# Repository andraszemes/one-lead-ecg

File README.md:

# One Lead ECG

The objective of this project was to create a working single lead EKG. The work process was divided into several stages to provide clarity and a productive development framework. Firstly, the hardware had to be layed out, manufactured and constructed. Then followed the phase of software design, development and deployment on different application layers. The finished product encompasses both physical and intellectual components.

The device measures biopotentials using body-surface electrodes. After amplification the signal is processed and filtered by a programmable microchip. Next, the filtered data gets transferred into the computer, where a program plots out the resulting graph. The input stream can be saved for later use either as a visual snapshot or as a data file.

A lot can be learned from such a comprehensive, theoretically and practically challanging undertaking. Let the subject of this project be a testimony to the importance of interdisciplinary research and exchange of knowledge.

## Hardware

The circuit schematic and PCB design is available in the /hardware folder. The design files were created in Eagle.

### Prerequisites

For the desktop application make sure the Java Runtime Environment is installed.

## Web interface demo

The web interface is currently available on [the demo site](http://ekg.epizy.com/).

### Desktop app installation

The distribution binaries are located in /software/heart_rate_monitor/dist. Alternatively you can use the Serial Plotter of the Arduino IDE.

Linux terminal:

```
./heart_rate_monitor
```

Windows CLI:

```
heart_rate_monitor.exe
```

## Built With

* [Arduino IDE](https://www.arduino.cc/en/main/software) - Microchip programming
* [Eagle](https://www.autodesk.com/products/eagle/overview) - PCB design software
* [Processing](https://processing.org/) - Visual desktop application
* [Bootstrap](https://getbootstrap.com/) - The web framework used
* [CanvasJS](https://canvasjs.com/) - Graph plotting API on the web

## Authors

* **András Zemes** - *Project developer* - [andraszemes](https://github.com/andraszemes)

## Acknowledgments

* [Scott W harden](https://www.swharden.com/wp/)
* [Casey Kuhns](https://github.com/sparkfun/AD8232_Heart_Rate_Monitor)
* [Pieter Pas](https://github.com/tttapa/Filters)

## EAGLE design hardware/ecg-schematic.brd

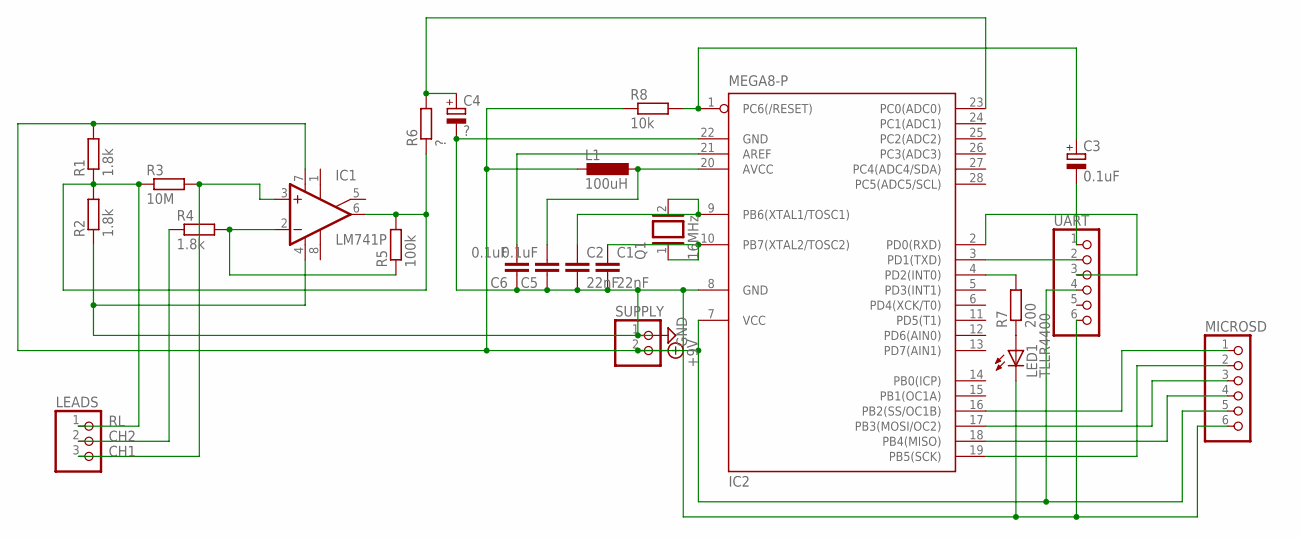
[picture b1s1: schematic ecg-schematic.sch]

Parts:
C1, C2: 22nF; C025-025X050
C3: 0.1uF; B45181A
C4: ?; ETR1
C5, C6: 0.1uF; C025-025X050
IC1: LM741P; DIL08
IC2: MEGA8-P; DIL28-3
L1: 100uH; 0204/5
LEADS: PINHD-1X3; 1X03
LED1: TLLR4400; LED3MM
MICROSD: PINHD-1X6; 1X06
Q1: 16MHz; QS
R1, R2, R4: 1.8k; 0204/7
R3: 10M; 0204/7
R5: 100k; 0204/7
R6: ?; 0204/7
R7: 200; 0204/7
R8: 10k; 0204/7
SUPPLY: PINHD-1X2; 1X02
UART: PINHD-1X6; 1X06

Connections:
+9V: IC1.7 (V+), IC2.7 (VCC), L1.2, MICROSD.5, R1.2, R8.1, SUPPLY.2, UART.4
CH1: IC1.3 (+IN), LEADS.3, R3.2
CH2: LEADS.2, R4.1
GND: C1.2, C2.2, C4.-, C5.1, C6.1, IC1.4 (V-), IC2.8 (GND), IC2.22 (GND), LED1.K (C), MICROSD.6, R2.1, SUPPLY.1, UART.6
unnamed: C2.1, IC2.9 (PB6(XTAL1/TOSC1)), Q1.2
unnamed: C1.1, IC2.10 (PB7(XTAL2/TOSC2)), Q1.1
unnamed: IC1.2 (-IN), R4.2, R5.1
unnamed: C3.-, UART.1
unnamed: C3.+, IC2.1 (PC6(/RESET)), R8.2
unnamed: IC2.3 (PD1(TXD)), UART.2
unnamed: IC2.2 (PD0(RXD)), UART.3
unnamed: C4.+, IC2.23 (PC0(ADC0)), R6.2
unnamed: IC2.16 (PB2(SS/OC1B)), MICROSD.1
unnamed: IC2.19 (PB5(SCK)), MICROSD.2
unnamed: IC2.17 (PB3(MOSI/OC2)), MICROSD.3
unnamed: IC2.18 (PB4(MISO)), MICROSD.4
unnamed: LED1.A, R7.1
unnamed: IC2.4 (PD2(INT0)), R7.2
unnamed: C5.2, IC2.20 (AVCC), L1.1
unnamed: C6.2, IC2.21 (AREF)
RL: IC1.6 (OUT), LEADS.1, R1.1, R2.2, R3.1, R5.2, R6.1

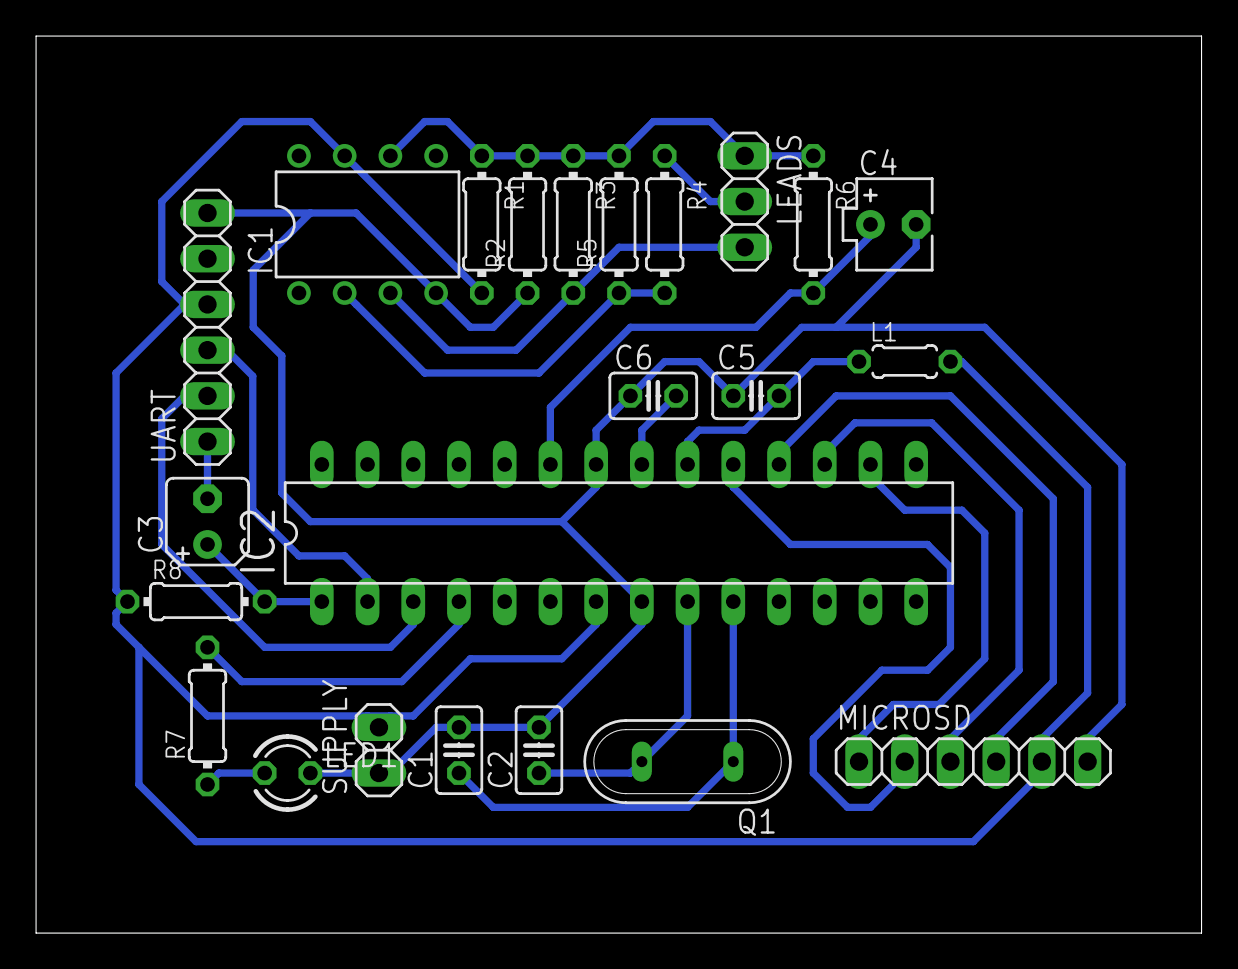
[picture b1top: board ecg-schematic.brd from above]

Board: 2 copper layers, 64.8 x 49.8 mm, 23 parts (0 on the bottom side), 21 nets.

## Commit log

2018-12-19 Initial commit.
2019-01-13 Add signal processing to documentation.
2019-01-21 Add docs pages.
2019-01-31 Add HW construction and introduction.
2019-02-04 Add software, hardware design components.
2019-02-07 Style changes. Add software section.
2019-02-14 Add software description. Fix title page. Add filters quotes. Add attachments.
2019-02-23 Add evaluation.
2019-02-25 Add results, conclusions, resume.
2019-02-28 Docs corrections. Add attachments.
2019-03-02 Update web page. Add server upload. Add link share. Add contact and about sections.
2019-03-02 Create Heart Rate Monitor executables. Change HRM graph scale. Remove BPM count.
2019-03-02 Add readme.
2019-03-02 Readme corrections. Arduino sketch update.
2019-03-02 Readme corrections.
2019-03-16 Documentation final corrections.
2019-04-08 Update readme.
